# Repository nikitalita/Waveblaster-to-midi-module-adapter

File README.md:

# Waveblaster Breakout Card
A waveblaster breakout card to enable the use of external midi modules on sound cards:

Tested and working; here's the BOM:

| Id   | Designator | Package                                     | Quantity | Designation     | Mouser:                                                      |
| ---- | ---------- | ------------------------------------------- | -------- | --------------- | ------------------------------------------------------------ |
| 1    | J7         | IDC-Header_2x13_P2.54mm_Horizontal-reversed | 1        | Wavetable Input | [5103310-6](https://www.mouser.com/ProductDetail/TE-Connectivity/5103310-6) |
| 2    | J1         | Jack_3.5mm_CUI_SJ1-3533NG_Horizontal        | 1        | Midi Out        | [490-SJ1-3533NG](https://www.mouser.com/ProductDetail/490-SJ1-3533NG) |
| 3    | R4,R3      | 220R THT resistor                           | 2        | 220R            |                                                              |
| 4    | J3         | CUI_RCJ-042                                 | 1        | Right In        | [490-RCJ-042](https://www.mouser.com/ProductDetail/490-RCJ-042) |
| 5    | J4         | CUI_RCJ-043                                 | 1        | Left In         | [490-RCJ-043](https://www.mouser.com/ProductDetail/490-RCJ-043) |

For the header, you also can just use 2.54mm pitch double row right angle header pins. For the resistors, just buy a through-hole resistor sample book on Amazon or something.

If you want to add on the midi in port (most sound cards do not have this connected), add:

- 1x H11L1M optocoupler : https://www.mouser.com/ProductDetail/onsemi-Fairchild/H11L1M
- 1x 220 Ohm THT Resistor
- 1x 280 Ohm THT Resistor
- 1x 1N4148 THT Diode: https://www.mouser.com/ProductDetail/onsemi-Fairchild/1N4148

It's not advised to add on the audio output ports (for audio input into the synth), as only ONE sound card is known to make use of these: the MediaTriX AudioTriX 3D-XG, and it is very rare.

For the MIDI ports, you want a Type "A" 3.5mm to DIN adapter, like this one: https://www.amazon.com/ZAWDIO-Breakout-LittleBits-Female-Electribe/dp/B08WHSP7ZL/
Make sure that it is not Type "B", as this type will not work.

For the ribbon cable to connect the waveblaster header, Just use a 26 pin IDC cable. This one worked well for me: https://www.amazon.com/gp/product/B01AG9GXV4/ref=ppx_yo_dt_b_asin_title_o02_s00?ie=UTF8&psc=1

For the bracket, use the stencil file in bracket to 3D print it out. If you decide to make a metal one, be sure to add insulating rubber rings between the ports and the bracket, as this board is not intended to be grounded to the case.

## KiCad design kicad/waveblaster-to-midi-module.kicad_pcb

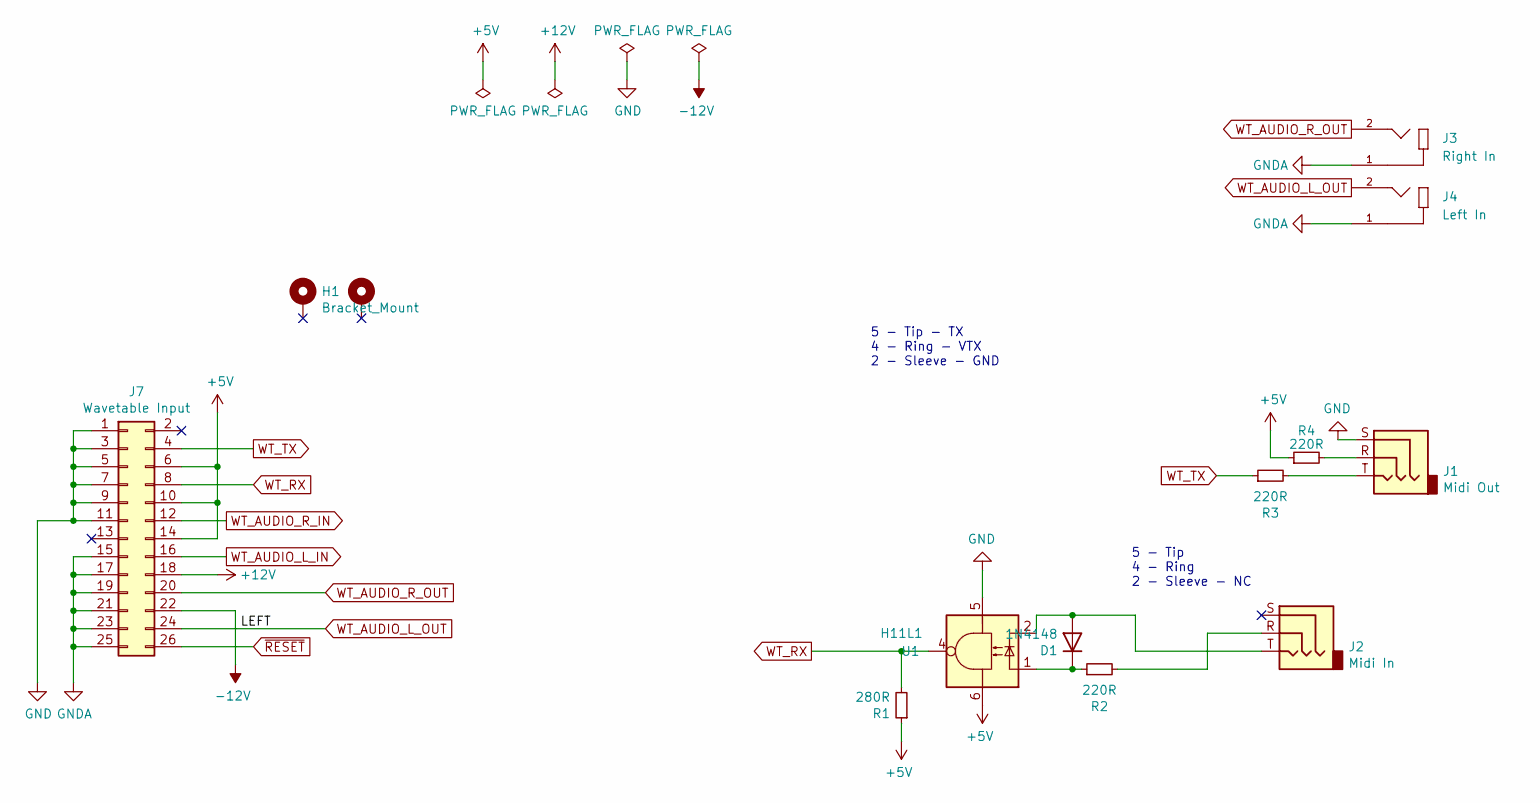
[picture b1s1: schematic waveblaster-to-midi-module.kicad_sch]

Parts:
D1: 1N4148; D_DO-35_SOD27_P5.08mm_Vertical_AnodeUp
H1: Bracket_Mount; bracket footprint
J1: Midi Out; Jack_3.5mm_CUI_SJ1-3533NG_Horizontal
J2: Midi In; Jack_3.5mm_CUI_SJ1-3533NG_Horizontal
J3: Right In; CUI_RCJ-04X
J4: Left In; CUI_RCJ-043
J7: Wavetable Input; IDC-Header_2x13_P2.54mm_Horizontal-reversed
R1: 280R; R_Axial_DIN0207_L6.3mm_D2.5mm_P7.62mm_Horizontal; Mouser 667-ERJ-6ENF1002V
R2, R3, R4: 220R; R_Axial_DIN0207_L6.3mm_D2.5mm_P7.62mm_Horizontal; Mouser 667-ERJ-6ENF2200V
U1: H11L1; H11L1M-DIP8

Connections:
+5V: J7.6, J7.10, J7.14, R1.1, R4.1, U1.6
+12V: J7.18
-12V: J7.22
GND: J1.S, J7.1, J7.3, J7.5, J7.7, J7.9, J7.11, U1.5
GNDA: J3.1, J4.1, J7.15, J7.17, J7.19, J7.21, J7.23, J7.25
unnamed: D1.1 (K), R2.1, U1.1
unnamed: D1.2 (A), J2.T, U1.2
unnamed: J1.R, R4.2
unnamed: J1.T, R3.2
unnamed: J2.R, R2.2
WT_AUDIO_L_IN: J7.16
WT_AUDIO_L_OUT: J4.2, J7.24
WT_AUDIO_R_IN: J7.12
WT_AUDIO_R_OUT: J3.2, J7.20
WT_RX: J7.8, R1.2, U1.4
WT_TX: J7.4, R3.1
~RESET: J7.26

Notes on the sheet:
5 - Tip 4 - Ring 2 - Sleeve - NC
5 - Tip - TX 4 - Ring - VTX 2 - Sleeve - GND

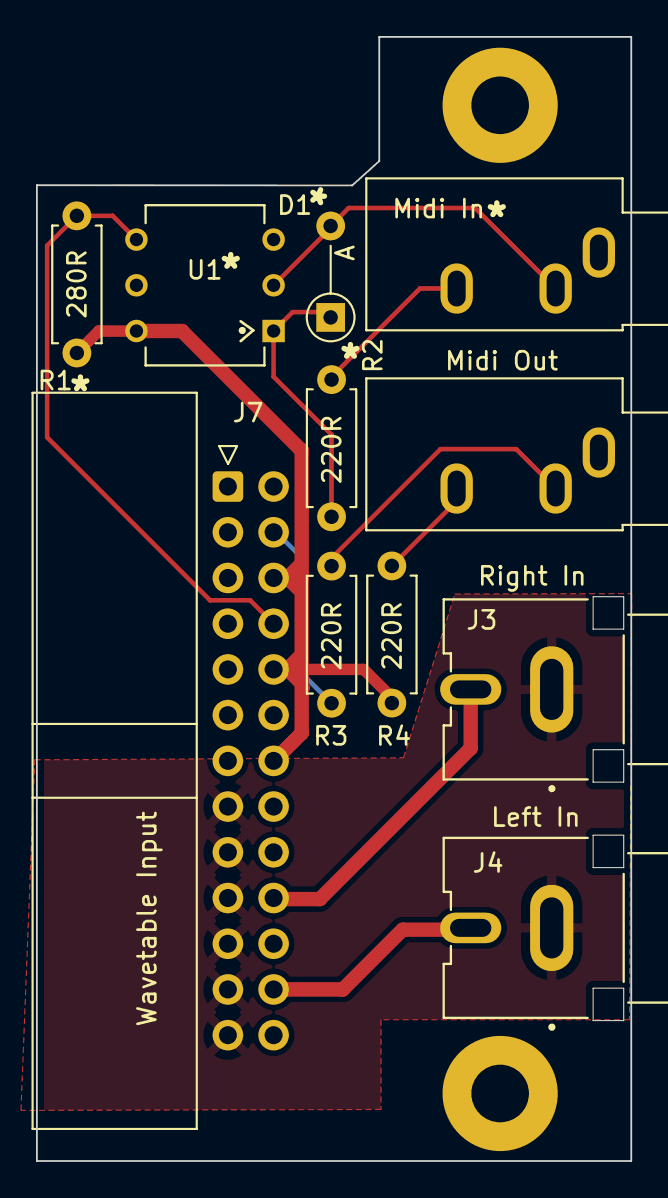
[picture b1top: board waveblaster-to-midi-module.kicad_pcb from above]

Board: 2 copper layers, 33.0 x 62.4 mm, 12 parts (0 on the bottom side), 12 nets.

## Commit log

2022-09-07 final board revision, update readme
2022-09-08 Adjust outline of PCB, finalize bracket
2022-09-08 regenerate gerbers
2022-09-16 fix clearance issues, fix bracket
2022-09-21 Fix bracket, update bracket footprint, update JLCPCB gerbers
2022-10-08 v2.0: low profile
2023-02-08 old?
